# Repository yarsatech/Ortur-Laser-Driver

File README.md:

# Ortur Laser Driver PCB 

This is a homebrew PCB replacement for the LU2-4 LF laser module driver PCB used by ortur lasers.

## What does it look like.

## The schematic

You can find the schematic PDF and gerbers in the [releases](https://github.com/yarsatech/Ortur-Laser-Driver/releases).

## 
Hope this helps :)

Proudly designed and made in Nepal by Yarsa Tech.

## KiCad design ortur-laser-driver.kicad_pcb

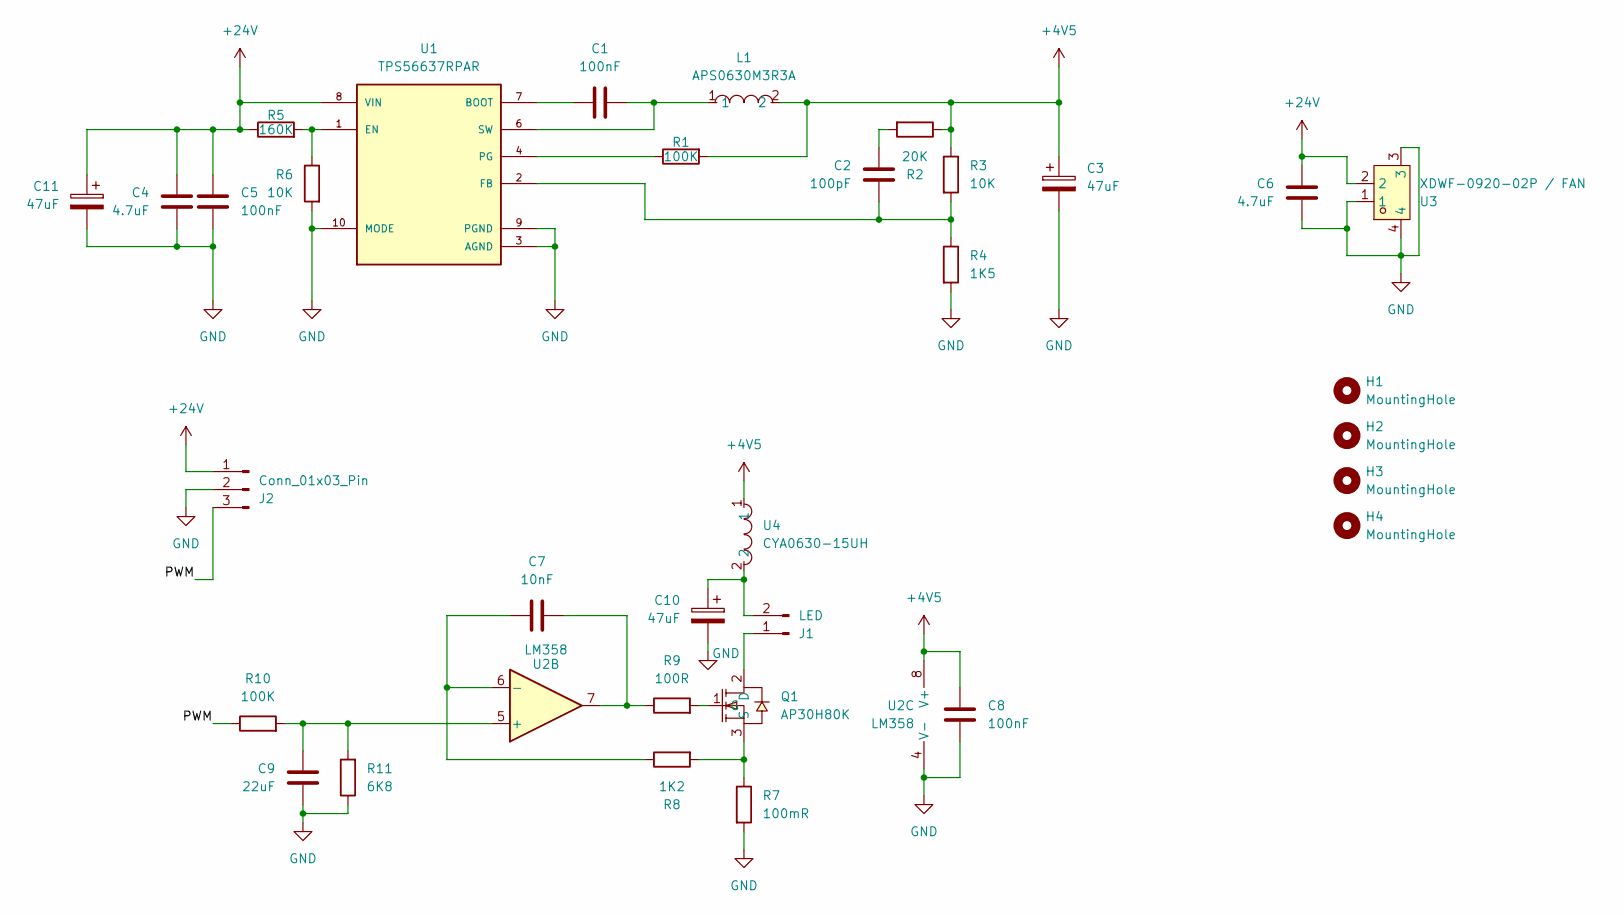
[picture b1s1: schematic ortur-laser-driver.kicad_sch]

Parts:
C1, C5, C8: 100nF; C_0805_2012Metric
C2: 100pF; C_0805_2012Metric
C3, C10: 47uF; CP_Elec_5x5.4
C4, C6: 4.7uF; C_0805_2012Metric
C7: 10nF; C_0805_2012Metric
C9: 22uF; C_0805_2012Metric
C11: 47uF; CP_Elec_6.3x7.7
H1, H2, H3, H4: MountingHole; MountingHole_2.7mm_M2.5
J1: LED; JST_EH_S2B-EH_1x02_P2.50mm_Horizontal
J2: Conn_01x03_Pin; JST_XH_B3B-XH-A_1x03_P2.50mm_Vertical
L1: APS0630M3R3A; IND-SMD_L7.7-W6.6_APS0630; MPN APS0630M3R3A; LCSC Part C47327202
Q1: AP30H80K; TO-252-2_L6.6-W6.1-P4.60-LS10.0-BR-CW; MPN AP30H80K; LCSC Part C2849564
R1, R10: 100K; R_0603_1608Metric
R2: 20K; R_0603_1608Metric
R3, R6: 10K; R_0603_1608Metric
R4: 1K5; R_0603_1608Metric
R5: 160K; R_0603_1608Metric
R7: 100mR; R_2512_6332Metric
R8: 1K2; R_0603_1608Metric
R9: 100R; R_0603_1608Metric
R11: 6K8; R_0603_1608Metric
U1: TPS56637RPAR; CONV_TPS56637RPAR; PARTREV A
U2: LM358; SOIC-8_3.9x4.9mm_P1.27mm
U3: XDWF-0920-02P / FAN; CONN-SMD_XDWF-0920-02P; MPN XDWF-0920-02P; LCSC Part C7527581
U4: CYA0630-15UH; IND-SMD_L7.2-W6.6_GPSR07X0; MPN CYA0630-15UH; LCSC Part C5189959

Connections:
+4V5: C3.1, C8.2, L1.2, R1.2, R2.1, R3.1, U2.8 (V+), U4.1
+24V: C4.2, C5.2, C6.2, C11.1, J2.1, R5.1, U1.8 (VIN), U3.2
/PWM: J2.3, R10.1
GND: C3.2, C4.1, C5.1, C6.1, C8.1, C9.1, C10.2, C11.2, J2.2, R4.2, R6.2, R7.2, R11.1, U1.3 (AGND), U1.9 (PGND), U1.10 (MODE), U2.4 (V-), U3.1, U3.3, U3.4
unnamed: C2.1, R2.2
unnamed: C7.1, R9.1, U2.7
unnamed: J1.1, Q1.2 (D)
unnamed: C10.1, J1.2, U4.2
unnamed: Q1.1 (G), R9.2
unnamed: Q1.3 (S), R7.1, R8.2
unnamed: C1.1, U1.7 (BOOT)
unnamed: R5.2, R6.1, U1.1 (EN)
unnamed: C2.2, R3.2, R4.1, U1.2 (FB)
unnamed: R1.1, U1.4 (PG)
unnamed: C1.2, L1.1, U1.6 (SW)
unnamed: C9.2, R10.2, R11.2, U2.5 (+)
unnamed: C7.2, R8.1, U2.6 (-)

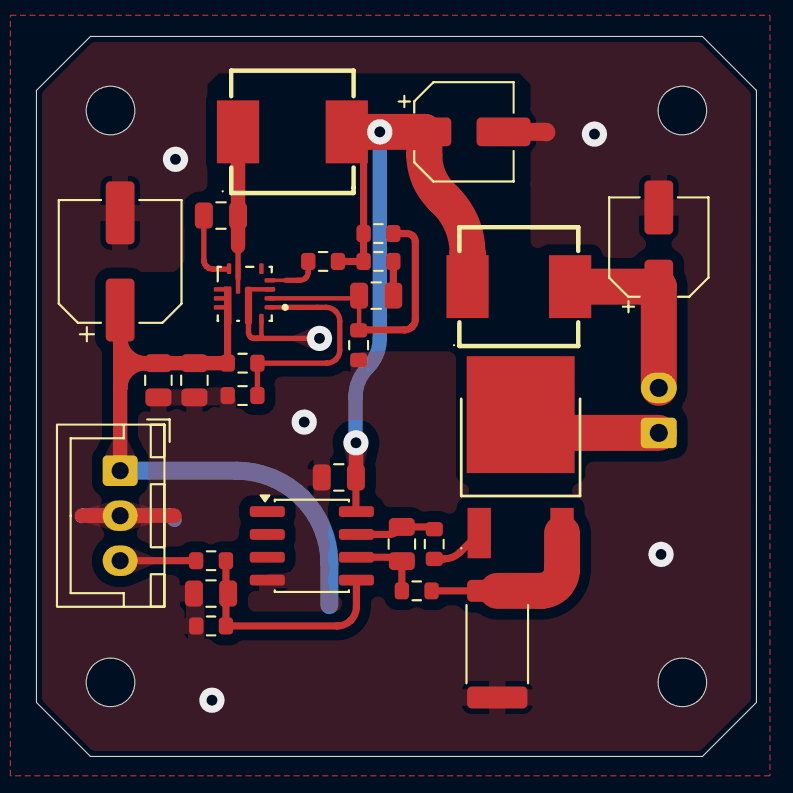
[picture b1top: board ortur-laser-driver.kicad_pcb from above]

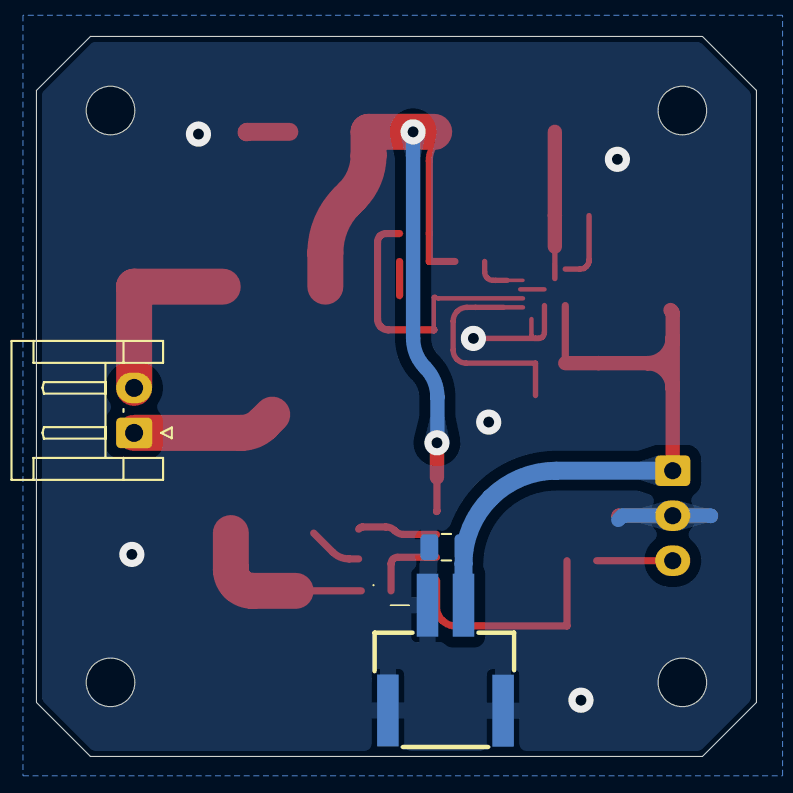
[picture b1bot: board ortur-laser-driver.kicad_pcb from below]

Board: 2 copper layers, 40.0 x 40.0 mm, 34 parts (3 on the bottom side), 17 nets.
